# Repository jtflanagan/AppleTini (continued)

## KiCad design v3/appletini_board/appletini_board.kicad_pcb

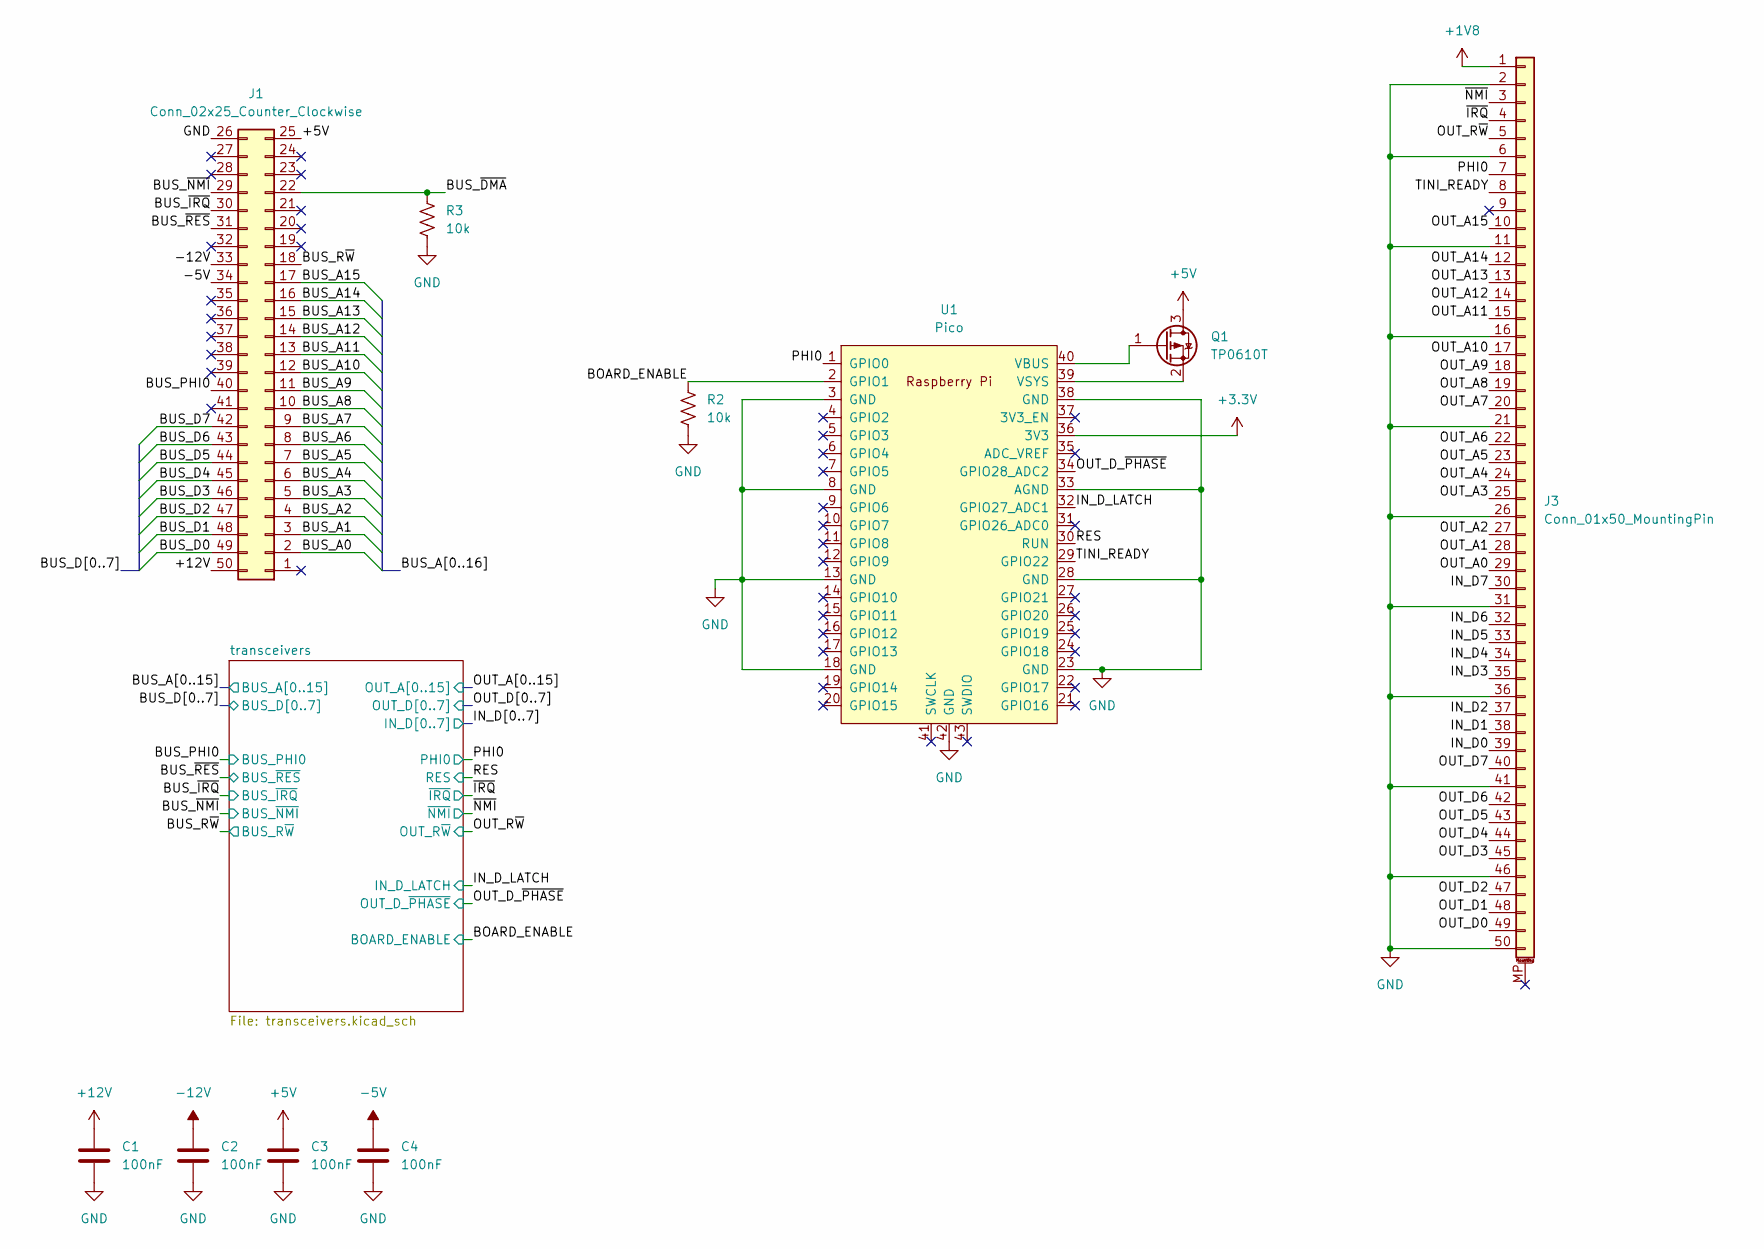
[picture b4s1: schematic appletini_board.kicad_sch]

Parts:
C1, C2, C3, C4: 100nF; C_1206_3216Metric; LCSC C24497
J1: Conn_02x25_Counter_Clockwise; AppleIIBus_Edge
J3: Conn_01x50_MountingPin; Hirose_FH12-50S-0.5SH_1x50-1MP_P0.50mm_Horizontal; LCSC C202116
Q1: TP0610T; SOT-23; LCSC C5261054
R2, R3: 10k; R_0402_1005Metric; LCSC C2991755
U1: Pico; RPi_Pico_SMD_TH; LCSC C7203002

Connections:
+1V8: J3.1; also elsewhere on the board
+3.3V: U1.36 (3V3); also elsewhere on the board
+5V: C3.1, J1.25, Q1.3 (D); also elsewhere on the board
+12V: C1.1, J1.50
-5V: C4.1, J1.34
-12V: C2.1, J1.33
/BOARD_ENABLE: R2.1, U1.2 (GPIO1); also elsewhere on the board
/BUS_A0: J1.2; also elsewhere on the board
/BUS_A1: J1.3; also elsewhere on the board
/BUS_A2: J1.4; also elsewhere on the board
/BUS_A3: J1.5; also elsewhere on the board
/BUS_A4: J1.6; also elsewhere on the board
/BUS_A5: J1.7; also elsewhere on the board
/BUS_A6: J1.8; also elsewhere on the board
/BUS_A7: J1.9; also elsewhere on the board
/BUS_A8: J1.10; also elsewhere on the board
/BUS_A9: J1.11; also elsewhere on the board
/BUS_A10: J1.12; also elsewhere on the board
/BUS_A11: J1.13; also elsewhere on the board
/BUS_A12: J1.14; also elsewhere on the board
/BUS_A13: J1.15; also elsewhere on the board
/BUS_A14: J1.16; also elsewhere on the board
/BUS_A15: J1.17; also elsewhere on the board
/BUS_D0: J1.49; also elsewhere on the board
/BUS_D1: J1.48; also elsewhere on the board
/BUS_D2: J1.47; also elsewhere on the board
/BUS_D3: J1.46; also elsewhere on the board
/BUS_D4: J1.45; also elsewhere on the board
/BUS_D5: J1.44; also elsewhere on the board
/BUS_D6: J1.43; also elsewhere on the board
/BUS_D7: J1.42; also elsewhere on the board
/BUS_PHI0: J1.40; also elsewhere on the board
/BUS_R~W: J1.18; also elsewhere on the board
/BUS_~DMA: J1.22, R3.1
/BUS_~IRQ: J1.30; also elsewhere on the board
/BUS_~NMI: J1.29; also elsewhere on the board
/BUS_~RES: J1.31; also elsewhere on the board
/IN_D0: J3.39; also elsewhere on the board
/IN_D1: J3.38; also elsewhere on the board
/IN_D2: J3.37; also elsewhere on the board
/IN_D3: J3.35; also elsewhere on the board
/IN_D4: J3.34; also elsewhere on the board
/IN_D5: J3.33; also elsewhere on the board
/IN_D6: J3.32; also elsewhere on the board
/IN_D7: J3.30; also elsewhere on the board
/IN_D_LATCH: U1.32 (GPIO27_ADC1); also elsewhere on the board
/OUT_A0: J3.29; also elsewhere on the board
/OUT_A1: J3.28; also elsewhere on the board
/OUT_A2: J3.27; also elsewhere on the board
/OUT_A3: J3.25; also elsewhere on the board
/OUT_A4: J3.24; also elsewhere on the board
/OUT_A5: J3.23; also elsewhere on the board
/OUT_A6: J3.22; also elsewhere on the board
/OUT_A7: J3.20; also elsewhere on the board
/OUT_A8: J3.19; also elsewhere on the board
/OUT_A9: J3.18; also elsewhere on the board
/OUT_A10: J3.17; also elsewhere on the board
/OUT_A11: J3.15; also elsewhere on the board
/OUT_A12: J3.14; also elsewhere on the board
/OUT_A13: J3.13; also elsewhere on the board
/OUT_A14: J3.12; also elsewhere on the board
/OUT_A15: J3.10; also elsewhere on the board
/OUT_D0: J3.49; also elsewhere on the board
/OUT_D1: J3.48; also elsewhere on the board
/OUT_D2: J3.47; also elsewhere on the board
/OUT_D3: J3.45; also elsewhere on the board
/OUT_D4: J3.44; also elsewhere on the board
/OUT_D5: J3.43; also elsewhere on the board
/OUT_D6: J3.42; also elsewhere on the board
/OUT_D7: J3.40; also elsewhere on the board
/OUT_D_~PHASE: U1.34 (GPIO28_ADC2); also elsewhere on the board
/OUT_R~W: J3.5; also elsewhere on the board
/PHI0: J3.7, U1.1 (GPIO0); also elsewhere on the board
/RES: U1.30 (RUN); also elsewhere on the board
/TINI_READY: J3.8, U1.29 (GPIO22)
/~IRQ: J3.4; also elsewhere on the board
/~NMI: J3.3; also elsewhere on the board
GND: C1.2, C2.2, C3.2, C4.2, J1.26, J3.2, J3.6, J3.11, J3.16, J3.21, J3.26, J3.31, J3.36, J3.41, J3.46, J3.50, R2.2, R3.2, U1.3 (GND), U1.8 (GND), U1.13 (GND), U1.18 (GND), U1.23 (GND), U1.28 (GND), U1.33 (AGND), U1.38 (GND), U1.42 (GND); also elsewhere on the board
unnamed: Q1.1 (G), U1.40 (VBUS)
unnamed: Q1.2 (S), U1.39 (VSYS)

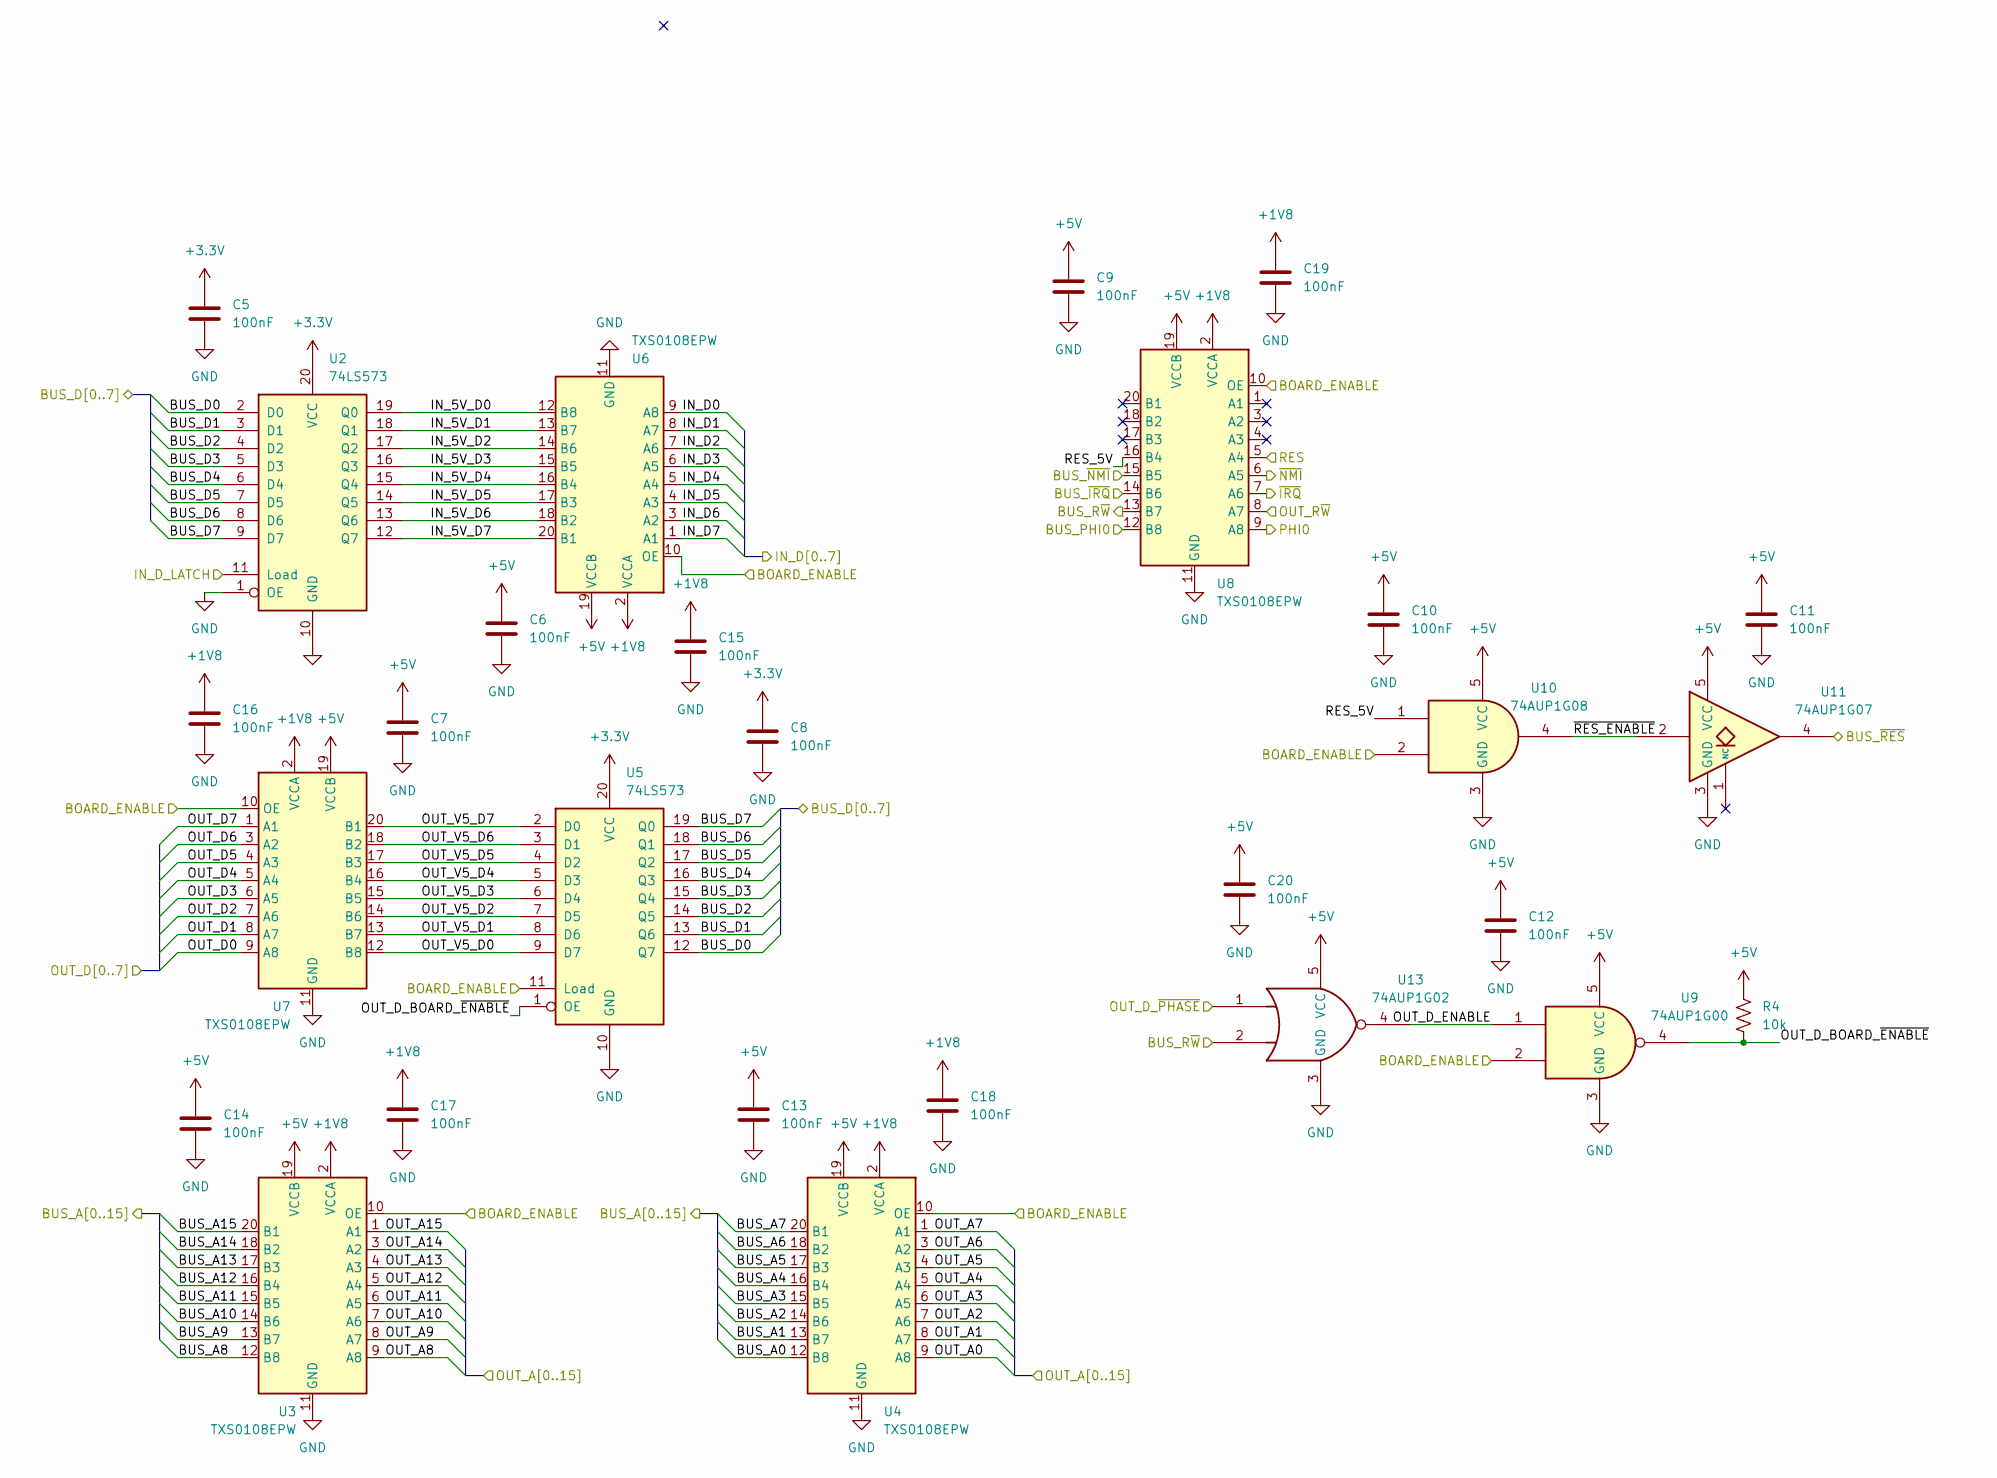
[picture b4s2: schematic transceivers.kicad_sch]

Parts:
C5, C6, C7, C8, C9, C10, C11, C12, C13, C14, C15, C16, C17, C18, C19, C20: 100nF; C_1206_3216Metric; LCSC C24497
R4: 10k; R_0402_1005Metric; LCSC C2991755
U2, U5: 74LS573; TSSOP-20_4.4x6.5mm_P0.65mm; LCSC C113280
U3, U4, U6, U7, U8: TXS0108EPW; TSSOP-20_4.4x6.5mm_P0.65mm; LCSC C17206
U9: 74AUP1G00; SOT-353_SC-70-5; LCSC C460514
U10: 74AUP1G08; SOT-353_SC-70-5; LCSC C233638
U11: 74AUP1G07; SOT-23-5; LCSC C242266
U13: 74AUP1G02; SOT-353_SC-70-5; LCSC C460515

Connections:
+1V8: C15.1, C16.1, C17.1, C18.1, C19.1, U3.2 (VCCA), U4.2 (VCCA), U6.2 (VCCA), U7.2 (VCCA), U8.2 (VCCA); also elsewhere on the board
+3.3V: C5.1, C8.1, U2.20 (VCC), U5.20 (VCC); also elsewhere on the board
+5V: C6.1, C7.1, C9.1, C10.1, C11.1, C12.1, C13.1, C14.1, C20.1, R4.1, U3.19 (VCCB), U4.19 (VCCB), U6.19 (VCCB), U7.19 (VCCB), U8.19 (VCCB), U9.5 (VCC), U10.5 (VCC), U11.5 (VCC), U13.5 (VCC); also elsewhere on the board
/BOARD_ENABLE: U3.10 (OE), U4.10 (OE), U5.11 (Load), U6.10 (OE), U7.10 (OE), U8.10 (OE), U9.2, U10.2; also elsewhere on the board
/BUS_A0: U4.12 (B8); also elsewhere on the board
/BUS_A1: U4.13 (B7); also elsewhere on the board
/BUS_A2: U4.14 (B6); also elsewhere on the board
/BUS_A3: U4.15 (B5); also elsewhere on the board
/BUS_A4: U4.16 (B4); also elsewhere on the board
/BUS_A5: U4.17 (B3); also elsewhere on the board
/BUS_A6: U4.18 (B2); also elsewhere on the board
/BUS_A7: U4.20 (B1); also elsewhere on the board
/BUS_A8: U3.12 (B8); also elsewhere on the board
/BUS_A9: U3.13 (B7); also elsewhere on the board
/BUS_A10: U3.14 (B6); also elsewhere on the board
/BUS_A11: U3.15 (B5); also elsewhere on the board
/BUS_A12: U3.16 (B4); also elsewhere on the board
/BUS_A13: U3.17 (B3); also elsewhere on the board
/BUS_A14: U3.18 (B2); also elsewhere on the board
/BUS_A15: U3.20 (B1); also elsewhere on the board
/BUS_D0: U2.2 (D0), U5.12 (Q7); also elsewhere on the board
/BUS_D1: U2.3 (D1), U5.13 (Q6); also elsewhere on the board
/BUS_D2: U2.4 (D2), U5.14 (Q5); also elsewhere on the board
/BUS_D3: U2.5 (D3), U5.15 (Q4); also elsewhere on the board
/BUS_D4: U2.6 (D4), U5.16 (Q3); also elsewhere on the board
/BUS_D5: U2.7 (D5), U5.17 (Q2); also elsewhere on the board
/BUS_D6: U2.8 (D6), U5.18 (Q1); also elsewhere on the board
/BUS_D7: U2.9 (D7), U5.19 (Q0); also elsewhere on the board
/BUS_PHI0: U8.12 (B8); also elsewhere on the board
/BUS_R~W: U8.13 (B7), U13.2; also elsewhere on the board
/BUS_~IRQ: U8.14 (B6); also elsewhere on the board
/BUS_~NMI: U8.15 (B5); also elsewhere on the board
/BUS_~RES: U11.4; also elsewhere on the board
/IN_D0: U6.9 (A8); also elsewhere on the board
/IN_D1: U6.8 (A7); also elsewhere on the board
/IN_D2: U6.7 (A6); also elsewhere on the board
/IN_D3: U6.6 (A5); also elsewhere on the board
/IN_D4: U6.5 (A4); also elsewhere on the board
/IN_D5: U6.4 (A3); also elsewhere on the board
/IN_D6: U6.3 (A2); also elsewhere on the board
/IN_D7: U6.1 (A1); also elsewhere on the board
/IN_D_LATCH: U2.11 (Load); also elsewhere on the board
/OUT_A0: U4.9 (A8); also elsewhere on the board
/OUT_A1: U4.8 (A7); also elsewhere on the board
/OUT_A2: U4.7 (A6); also elsewhere on the board
/OUT_A3: U4.6 (A5); also elsewhere on the board
/OUT_A4: U4.5 (A4); also elsewhere on the board
/OUT_A5: U4.4 (A3); also elsewhere on the board
/OUT_A6: U4.3 (A2); also elsewhere on the board
/OUT_A7: U4.1 (A1); also elsewhere on the board
/OUT_A8: U3.9 (A8); also elsewhere on the board
/OUT_A9: U3.8 (A7); also elsewhere on the board
/OUT_A10: U3.7 (A6); also elsewhere on the board
/OUT_A11: U3.6 (A5); also elsewhere on the board
/OUT_A12: U3.5 (A4); also elsewhere on the board
/OUT_A13: U3.4 (A3); also elsewhere on the board
/OUT_A14: U3.3 (A2); also elsewhere on the board
/OUT_A15: U3.1 (A1); also elsewhere on the board
/OUT_D0: U7.9 (A8); also elsewhere on the board
/OUT_D1: U7.8 (A7); also elsewhere on the board
/OUT_D2: U7.7 (A6); also elsewhere on the board
/OUT_D3: U7.6 (A5); also elsewhere on the board
/OUT_D4: U7.5 (A4); also elsewhere on the board
/OUT_D5: U7.4 (A3); also elsewhere on the board
/OUT_D6: U7.3 (A2); also elsewhere on the board
/OUT_D7: U7.1 (A1); also elsewhere on the board
/OUT_D_~PHASE: U13.1; also elsewhere on the board
/OUT_R~W: U8.8 (A7); also elsewhere on the board
/PHI0: U8.9 (A8); also elsewhere on the board
/RES: U8.5 (A4); also elsewhere on the board
/transceivers/IN_5V_D0: U2.19 (Q0), U6.12 (B8)
/transceivers/IN_5V_D1: U2.18 (Q1), U6.13 (B7)
/transceivers/IN_5V_D2: U2.17 (Q2), U6.14 (B6)
/transceivers/IN_5V_D3: U2.16 (Q3), U6.15 (B5)
/transceivers/IN_5V_D4: U2.15 (Q4), U6.16 (B4)
/transceivers/IN_5V_D5: U2.14 (Q5), U6.17 (B3)
/transceivers/IN_5V_D6: U2.13 (Q6), U6.18 (B2)
/transceivers/IN_5V_D7: U2.12 (Q7), U6.20 (B1)
/transceivers/OUT_D_BOARD_~ENABLE: R4.2, U5.1 (OE), U9.4
/transceivers/OUT_D_ENABLE: U9.1, U13.4
/transceivers/OUT_V5_D0: U5.9 (D7), U7.12 (B8)
/transceivers/OUT_V5_D1: U5.8 (D6), U7.13 (B7)
/transceivers/OUT_V5_D2: U5.7 (D5), U7.14 (B6)
/transceivers/OUT_V5_D3: U5.6 (D4), U7.15 (B5)
/transceivers/OUT_V5_D4: U5.5 (D3), U7.16 (B4)
/transceivers/OUT_V5_D5: U5.4 (D2), U7.17 (B3)
/transceivers/OUT_V5_D6: U5.3 (D1), U7.18 (B2)
/transceivers/OUT_V5_D7: U5.2 (D0), U7.20 (B1)
/transceivers/RES_5V: U8.16 (B4), U10.1
/transceivers/~RES_ENABLE: U10.4, U11.2
/~IRQ: U8.7 (A6); also elsewhere on the board
/~NMI: U8.6 (A5); also elsewhere on the board
GND: C5.2, C6.2, C7.2, C8.2, C9.2, C10.2, C11.2, C12.2, C13.2, C14.2, C15.2, C16.2, C17.2, C18.2, C19.2, C20.2, U2.1 (OE), U2.10 (GND), U3.11 (GND), U4.11 (GND), U5.10 (GND), U6.11 (GND), U7.11 (GND), U8.11 (GND), U9.3 (GND), U10.3 (GND), U11.3 (GND), U13.3 (GND); also elsewhere on the board

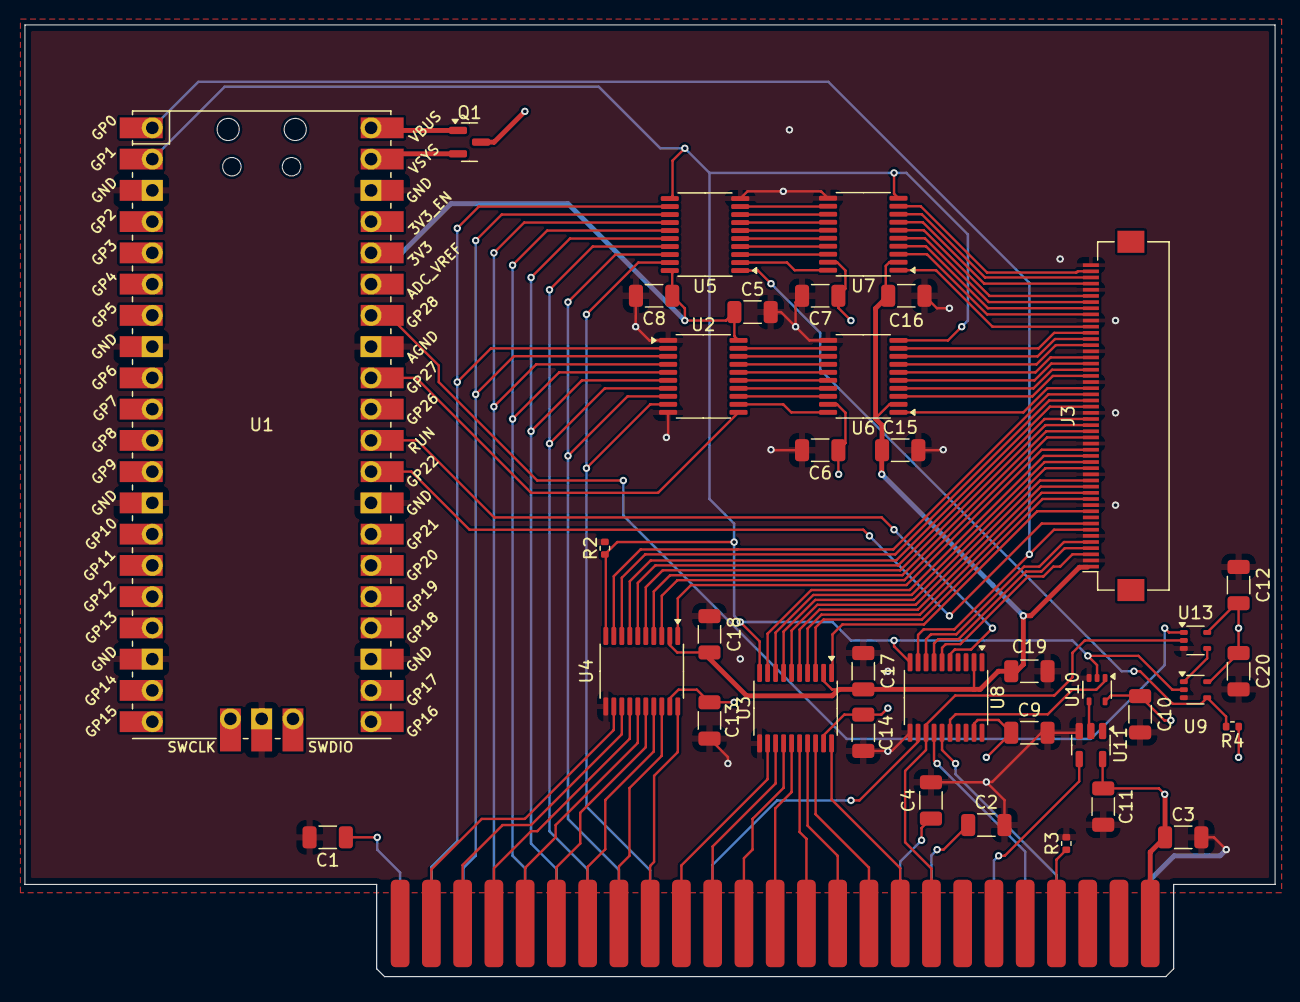
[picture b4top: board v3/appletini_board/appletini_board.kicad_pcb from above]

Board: 4 copper layers, 101.6 x 77.3 mm, 38 parts (0 on the bottom side), 100 nets.

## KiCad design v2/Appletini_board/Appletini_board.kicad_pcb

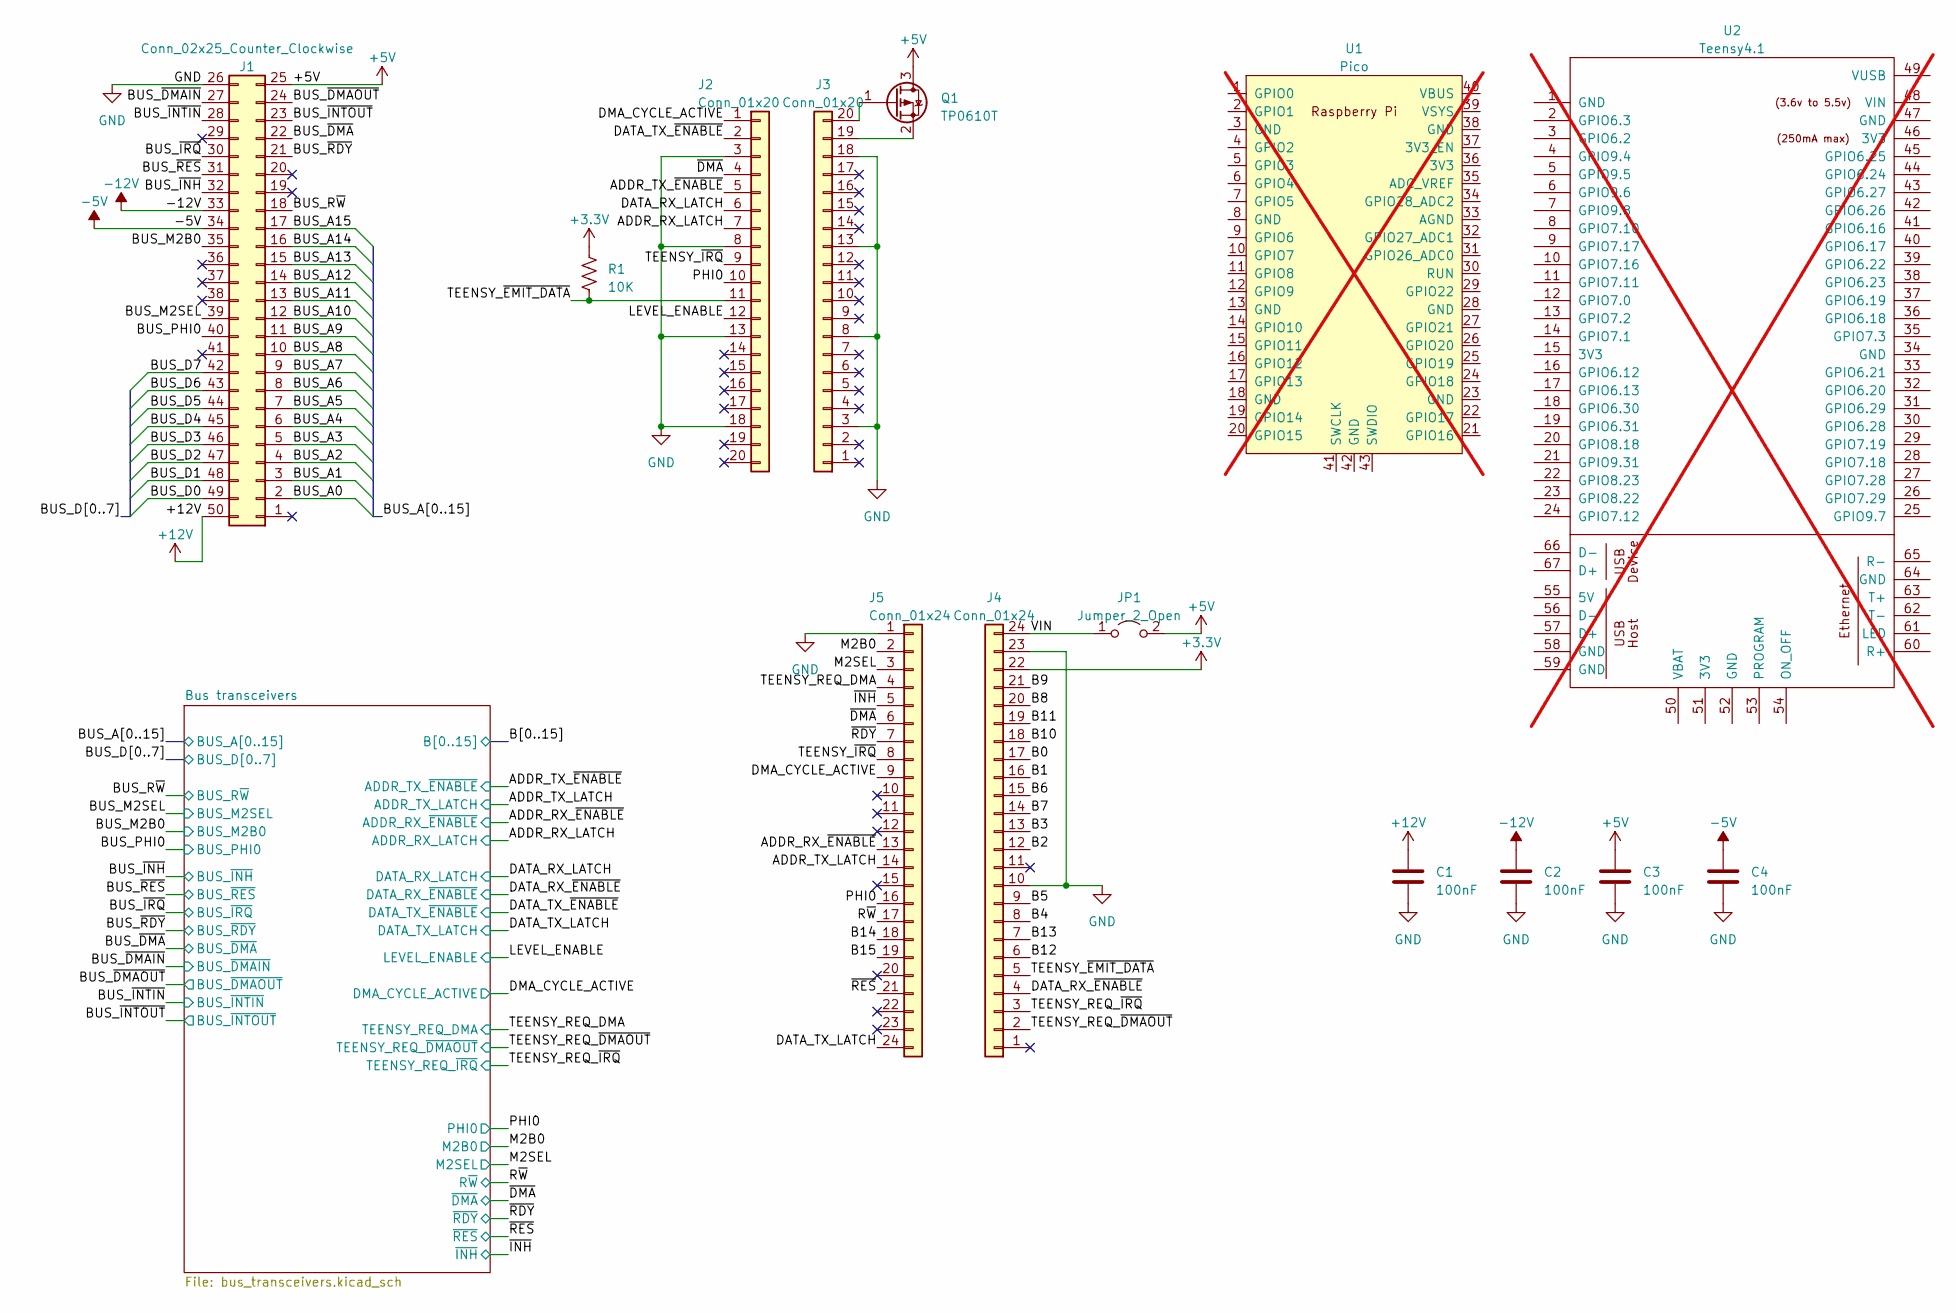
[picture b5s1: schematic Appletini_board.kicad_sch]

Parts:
C1, C2, C3, C4: 100nF; C_1206_3216Metric; LCSC C24497
J1: Conn_02x25_Counter_Clockwise; AppleIIBus_Edge
J2, J3: Conn_01x20; PinSocket_1x20_P2.54mm_Vertical; LCSC C50984
J4, J5: Conn_01x24; PinSocket_1x24_P2.54mm_Vertical; LCSC C2883741
JP1: Jumper_2_Open; PinHeader_1x02_P2.54mm_Vertical; LCSC C5360898
Q1: TP0610T; SOT-23; LCSC C5261054
R1: 10K; R_0402_1005Metric; LCSC C2991755
U1: Pico; RPi_Pico_SMD_TH; not fitted
U2: Teensy4.1; Teensy41; not fitted

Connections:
+3.3V: J4.22, R1.1; also elsewhere on the board
+5V: C3.1, J1.25, JP1.2 (B), Q1.3 (D); also elsewhere on the board
+12V: C1.1, J1.50
-5V: C4.1, J1.34
-12V: C2.1, J1.33
/ADDR_RX_LATCH: J2.7; also elsewhere on the board
/ADDR_RX_~ENABLE: J5.13; also elsewhere on the board
/ADDR_TX_LATCH: J5.14; also elsewhere on the board
/ADDR_TX_~ENABLE: J2.5; also elsewhere on the board
/B0: J4.17; also elsewhere on the board
/B1: J4.16; also elsewhere on the board
/B2: J4.12; also elsewhere on the board
/B3: J4.13; also elsewhere on the board
/B4: J4.8; also elsewhere on the board
/B5: J4.9; also elsewhere on the board
/B6: J4.15; also elsewhere on the board
/B7: J4.14; also elsewhere on the board
/B8: J4.20; also elsewhere on the board
/B9: J4.21; also elsewhere on the board
/B10: J4.18; also elsewhere on the board
/B11: J4.19; also elsewhere on the board
/B12: J4.6; also elsewhere on the board
/B13: J4.7; also elsewhere on the board
/B14: J5.18; also elsewhere on the board
/B15: J5.19; also elsewhere on the board
/BUS_A0: J1.2; also elsewhere on the board
/BUS_A1: J1.3; also elsewhere on the board
/BUS_A2: J1.4; also elsewhere on the board
/BUS_A3: J1.5; also elsewhere on the board
/BUS_A4: J1.6; also elsewhere on the board
/BUS_A5: J1.7; also elsewhere on the board
/BUS_A6: J1.8; also elsewhere on the board
/BUS_A7: J1.9; also elsewhere on the board
/BUS_A8: J1.10; also elsewhere on the board
/BUS_A9: J1.11; also elsewhere on the board
/BUS_A10: J1.12; also elsewhere on the board
/BUS_A11: J1.13; also elsewhere on the board
/BUS_A12: J1.14; also elsewhere on the board
/BUS_A13: J1.15; also elsewhere on the board
/BUS_A14: J1.16; also elsewhere on the board
/BUS_A15: J1.17; also elsewhere on the board
/BUS_D0: J1.49; also elsewhere on the board
/BUS_D1: J1.48; also elsewhere on the board
/BUS_D2: J1.47; also elsewhere on the board
/BUS_D3: J1.46; also elsewhere on the board
/BUS_D4: J1.45; also elsewhere on the board
/BUS_D5: J1.44; also elsewhere on the board
/BUS_D6: J1.43; also elsewhere on the board
/BUS_D7: J1.42; also elsewhere on the board
/BUS_M2B0: J1.35; also elsewhere on the board
/BUS_M2SEL: J1.39; also elsewhere on the board
/BUS_PHI0: J1.40; also elsewhere on the board
/BUS_R~W: J1.18; also elsewhere on the board
/BUS_~DMAIN: J1.27; also elsewhere on the board
/BUS_~DMAOUT: J1.24; also elsewhere on the board
/BUS_~DMA: J1.22; also elsewhere on the board
/BUS_~INH: J1.32; also elsewhere on the board
/BUS_~INTIN: J1.28; also elsewhere on the board
/BUS_~INTOUT: J1.23; also elsewhere on the board
/BUS_~IRQ: J1.30; also elsewhere on the board
/BUS_~RDY: J1.21; also elsewhere on the board
/BUS_~RES: J1.31; also elsewhere on the board
/DATA_RX_LATCH: J2.6; also elsewhere on the board
/DATA_RX_~ENABLE: J4.4; also elsewhere on the board
/DATA_TX_LATCH: J5.24; also elsewhere on the board
/DATA_TX_~ENABLE: J2.2; also elsewhere on the board
/DMA_CYCLE_ACTIVE: J2.1, J5.9; also elsewhere on the board
/LEVEL_ENABLE: J2.12; also elsewhere on the board
/M2B0: J5.2; also elsewhere on the board
/M2SEL: J5.3; also elsewhere on the board
/PHI0: J2.10, J5.16; also elsewhere on the board
/R~W: J5.17; also elsewhere on the board
/TEENSY_REQ_DMA: J5.4; also elsewhere on the board
/TEENSY_REQ_~DMAOUT: J4.2; also elsewhere on the board
/TEENSY_REQ_~IRQ: J4.3; also elsewhere on the board
/TEENSY_~EMIT_DATA: J2.11, J4.5, R1.2
/TEENSY_~IRQ: J2.9, J5.8
/VIN: J4.24, JP1.1 (A)
/~DMA: J2.4, J5.6; also elsewhere on the board
/~INH: J5.5; also elsewhere on the board
/~RDY: J5.7; also elsewhere on the board
/~RES: J5.21; also elsewhere on the board
GND: C1.2, C2.2, C3.2, C4.2, J1.26, J2.3, J2.8, J2.13, J2.18, J3.3, J3.8, J3.13, J3.18, J4.10, J4.23, J5.1; also elsewhere on the board
unnamed: J3.19, Q1.2 (S)
unnamed: J3.20, Q1.1 (G)
